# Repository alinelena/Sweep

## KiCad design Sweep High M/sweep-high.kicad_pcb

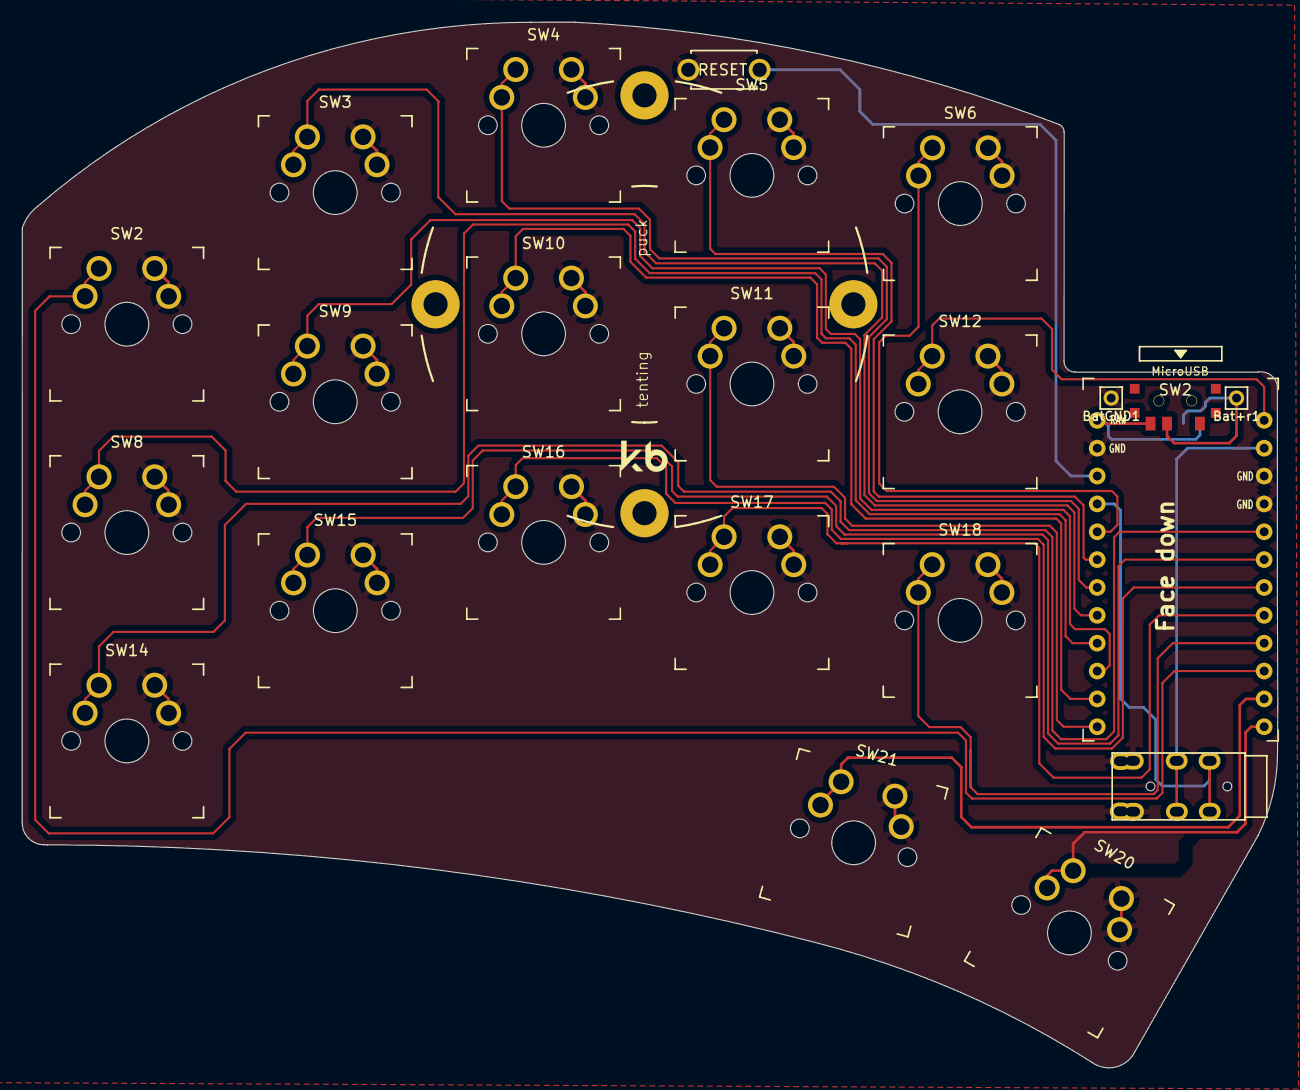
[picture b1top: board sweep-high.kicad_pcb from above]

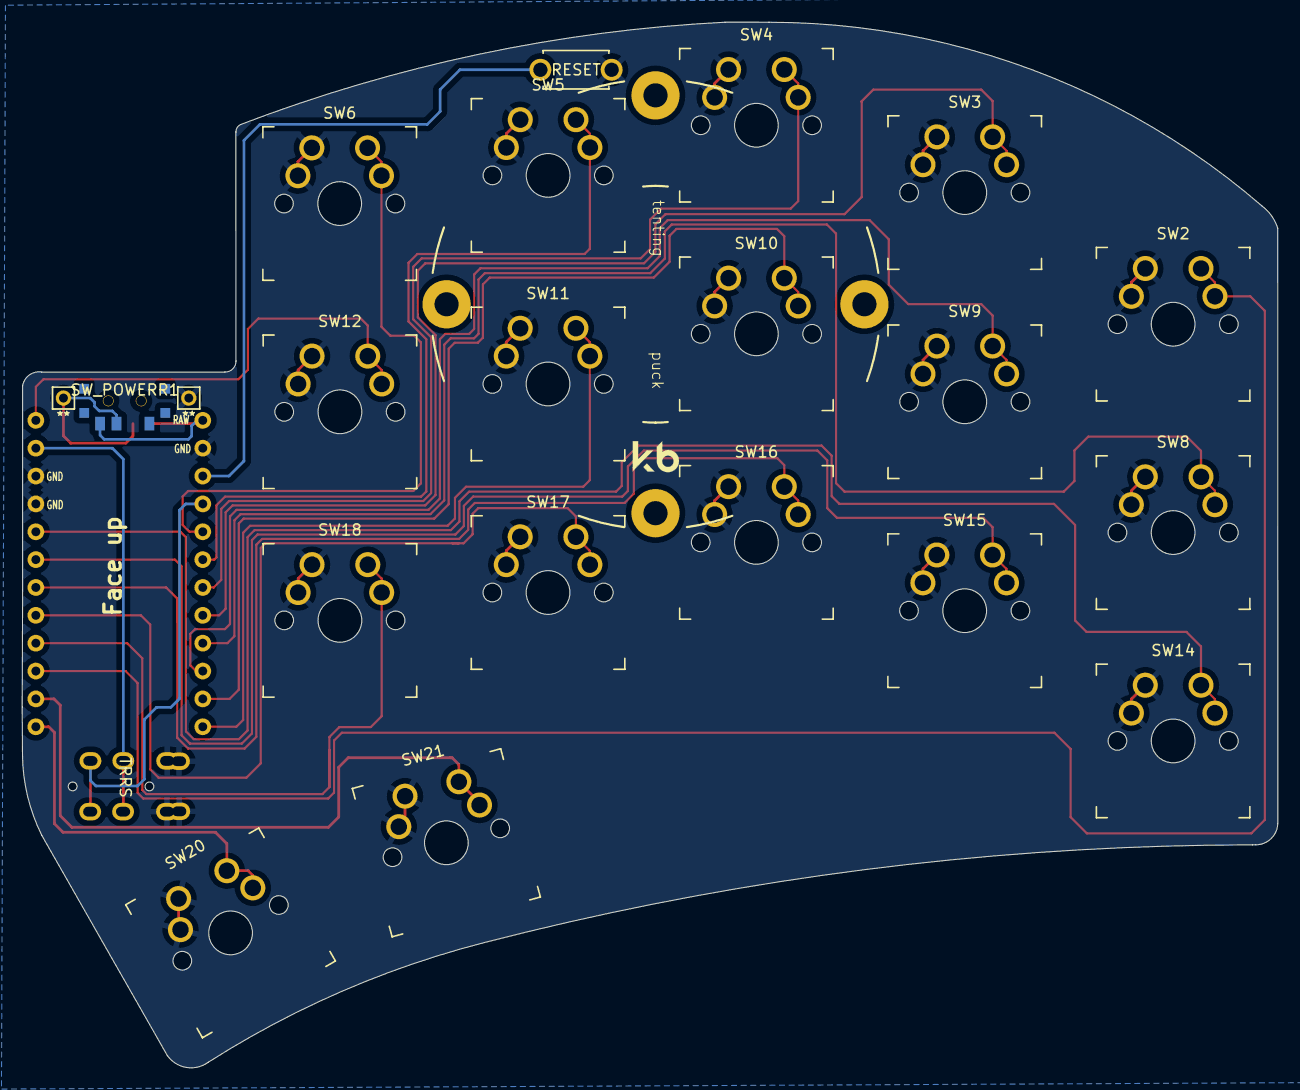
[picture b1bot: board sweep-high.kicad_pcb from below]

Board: 2 copper layers, 114.5 x 95.3 mm, 24 parts (2 on the bottom side), 23 nets.

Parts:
Bat+r1: MountingHole_Pad; 1pin_conn
BatGND1: MountingHole_Pad; 1pin_conn
J2: AudioJack4dpb; TRRS-PJ-DPB2
RSW1: SW_Push; ResetSW
SW2, SW3, SW4, SW5, SW6, SW8, SW9, SW10, SW11, SW12, SW14, SW15, SW16, SW17, SW18, SW20, SW21: SW_Push; SW_MX_reversible
SW2#2: SW_SPDT; SPDT_C128955r
SW_POWERR1: SW_SPDT; SPDT_C128955
U1: ProMicro-kbd; ProMicro_v3_min

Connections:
BT+_r: Bat+r1.1, SW2#2.2, SW_POWERR1.2
Switch1: SW2.1, U1.10
Switch2: SW3.1, U1.17
Switch3: SW4.1, U1.18
Switch4: SW5.1, U1.19
Switch5: SW6.1, U1.20
Switch6: SW8.1, U1.16
Switch7: SW9.1, U1.15
Switch8: SW10.1, U1.14
Switch9: SW11.1, U1.13
Switch10: SW12.1, U1.1
Switch11: SW14.1, U1.5
Switch12: SW15.1, U1.6
Switch13: SW16.1, U1.7
Switch14: SW17.1, U1.8
Switch15: SW18.1, U1.9
Switch16: SW21.1, U1.11
Switch17: SW20.1, U1.12
Switch18: J2.R1, U1.2
gnd: BatGND1.1, J2.S, J2.T, RSW1.1, SW2.2, SW3.2, SW4.2, SW5.2, SW6.2, SW8.2, SW9.2, SW10.2, SW11.2, SW12.2, SW14.2, SW15.2, SW16.2, SW17.2, SW18.2, SW20.2, SW21.2, U1.3, U1.4, U1.23
raw: SW2#2.3, SW_POWERR1.3, U1.24
reset: RSW1.2, U1.22
vcc: J2.R2, U1.21

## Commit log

2023-06-09 kicad 7 and rounded tracks for M
2023-06-10 add gerbers
